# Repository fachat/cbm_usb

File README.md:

# cbm_usb
USB solution for the Commodore Userport

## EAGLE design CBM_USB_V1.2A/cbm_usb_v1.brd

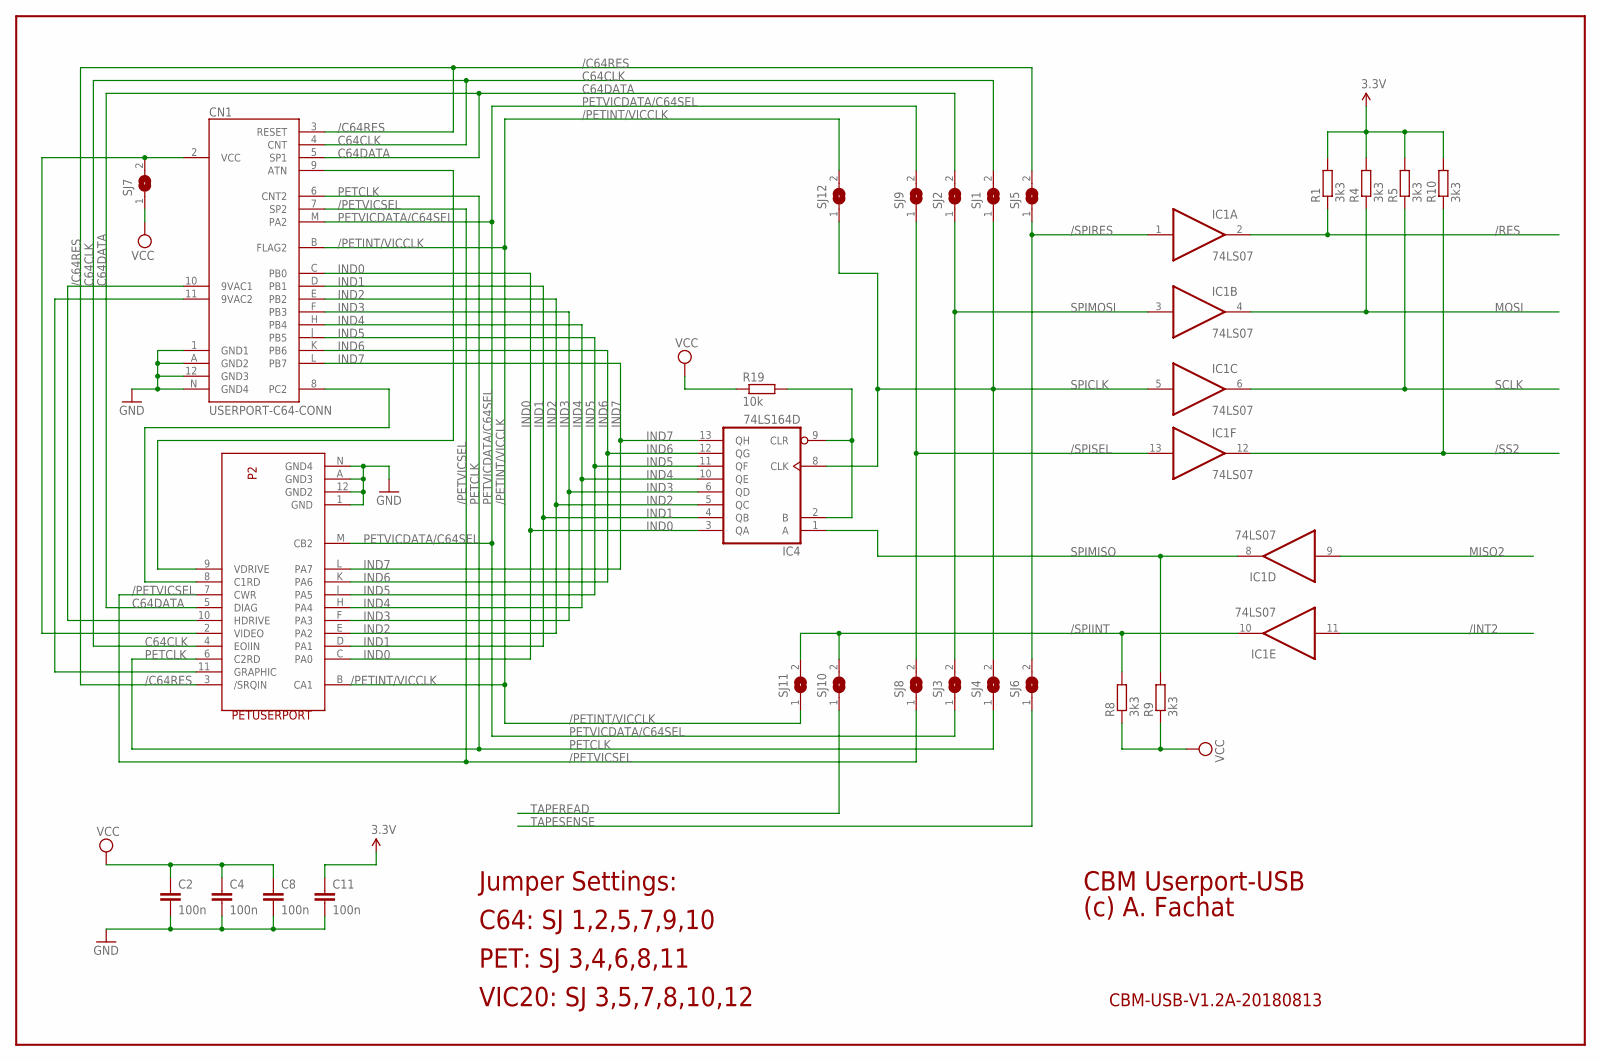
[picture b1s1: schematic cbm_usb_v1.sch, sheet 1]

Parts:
C2, C4, C8, C11: 100n; C050-025X075
CN1: USERPORT-C64-CONN; UPS24CONN
IC1: 74LS07; SO14
IC4: 74LS164D; SO14
P2: PETUSERPORT; FLAT24
R1, R4, R5, R8, R9, R10: 3k3; 0204/7
R19: 10k; 0204/7
SJ1, SJ2, SJ3, SJ4, SJ5, SJ6, SJ7, SJ8, SJ9, SJ10, SJ11, SJ12: SJW

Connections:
3.3V: C11.1, R1.2, R4.2, R5.2, R10.2; also elsewhere on the board
/C64RES: CN1.3 (RESET), P2.3 (/SRQIN), SJ5.2
/INT2: IC1.11 (I); also elsewhere on the board
/PETINT/VICCLK: CN1.B (FLAG2), P2.B (CA1), SJ11.1, SJ12.2
/PETVICSEL: CN1.7 (SP2), P2.7 (CWR), SJ8.1
/RES: IC1.2 (O), R1.1; also elsewhere on the board
/SPIINT: IC1.10 (O), R8.2, SJ10.2, SJ11.2
/SPIRES: IC1.1 (I), SJ5.1, SJ6.2
/SPISEL: IC1.13 (I), SJ8.2, SJ9.1
/SS2: IC1.12 (O), R10.1; also elsewhere on the board
C64CLK: CN1.4 (CNT), P2.4 (EOIIN), SJ1.2
C64DATA: CN1.5 (SP1), P2.5 (DIAG), SJ2.2
GND: C2.2, C4.2, C8.2, C11.2, CN1.1 (GND1), CN1.12 (GND3), CN1.A (GND2), CN1.N (GND4), IC1.7 (GND), IC4.7 (GND), P2.1 (GND), P2.12 (GND2), P2.A (GND3), P2.N (GND4); also elsewhere on the board
IND0: CN1.C (PB0), IC4.3 (QA), P2.C (PA0)
IND1: CN1.D (PB1), IC4.4 (QB), P2.D (PA1)
IND2: CN1.E (PB2), IC4.5 (QC), P2.E (PA2)
IND3: CN1.F (PB3), IC4.6 (QD), P2.F (PA3)
IND4: CN1.H (PB4), IC4.10 (QE), P2.H (PA4)
IND5: CN1.J (PB5), IC4.11 (QF), P2.J (PA5)
IND6: CN1.K (PB6), IC4.12 (QG), P2.K (PA6)
IND7: CN1.L (PB7), IC4.13 (QH), P2.L (PA7)
MISO2: IC1.9 (I); also elsewhere on the board
MOSI: IC1.4 (O), R4.1; also elsewhere on the board
unnamed: CN1.10 (9VAC1), P2.10 (HDRIVE)
unnamed: CN1.11 (9VAC2), P2.11 (GRAPHIC)
unnamed: CN1.2 (VCC), P2.2 (VIDEO), SJ7.2
unnamed: CN1.8 (PC2), P2.8 (C1RD)
unnamed: CN1.9 (ATN), P2.9 (VDRIVE)
unnamed: IC4.2 (B), IC4.9 (CLR), R19.2
PETCLK: CN1.6 (CNT2), P2.6 (C2RD), SJ4.1
PETVICDATA/C64SEL: CN1.M (PA2), P2.M (CB2), SJ3.1, SJ9.2
SCLK: IC1.6 (O), R5.1; also elsewhere on the board
SPICLK: IC1.5 (I), IC4.8 (CLK), SJ1.1, SJ4.2, SJ12.1
SPIMISO: IC1.8 (O), IC4.1 (A), R9.2
SPIMOSI: IC1.3 (I), SJ2.1, SJ3.2
TAPEREAD: SJ10.1; also elsewhere on the board
TAPESENSE: SJ6.1; also elsewhere on the board
VCC: C2.1, C4.1, C8.1, IC1.14 (VCC), IC4.14 (VCC), R8.1, R9.1, R19.1, SJ7.1; also elsewhere on the board

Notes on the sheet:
CBM-USB-V1.2A-20180813
CBM Userport-USB
(c) A. Fachat
Jumper Settings:
C64: SJ 1,2,5,7,9,10
PET: SJ 3,4,6,8,11
VIC20: SJ 3,5,7,8,10,12

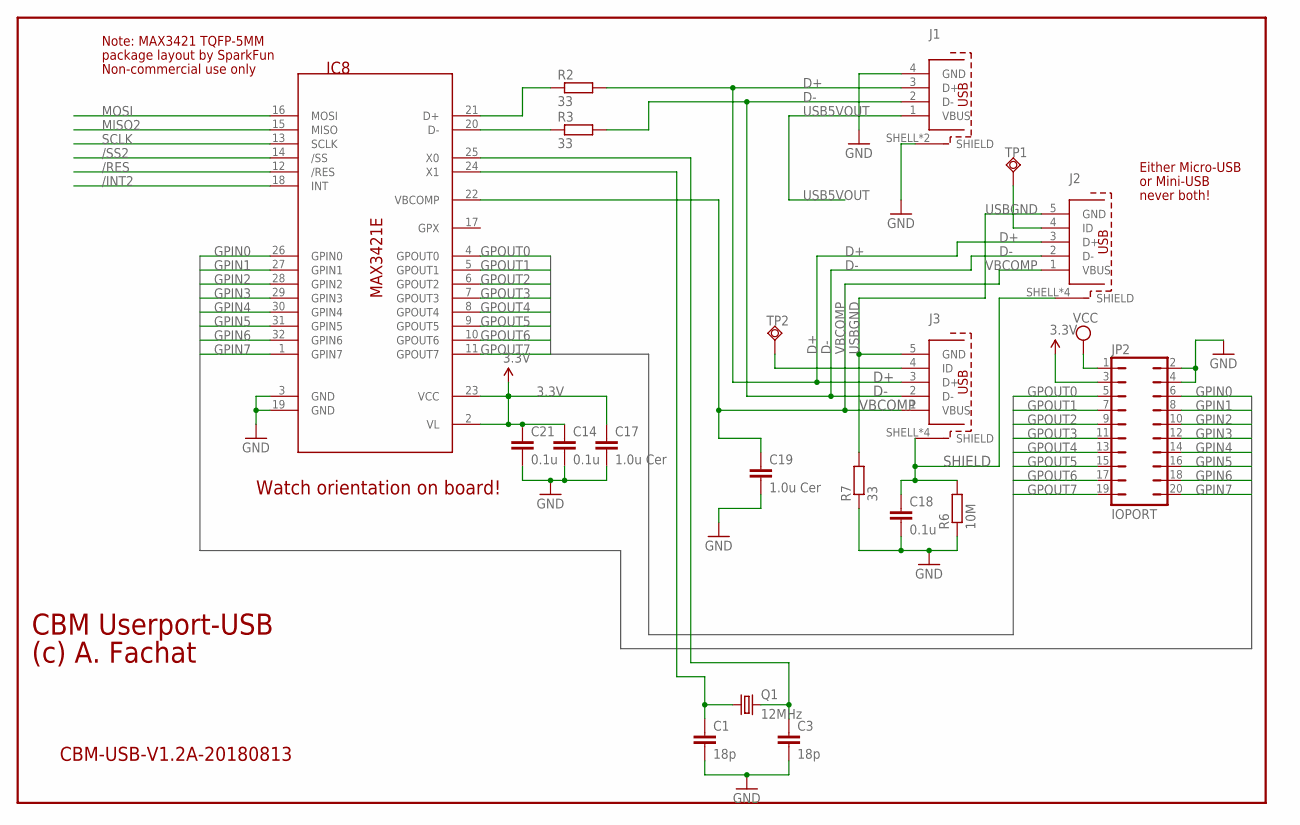
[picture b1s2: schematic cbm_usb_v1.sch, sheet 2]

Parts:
C1, C3: 18p; C050-025X075
C14, C18, C21: 0.1u; C050-025X075
C17, C19: 1.0u Cer; C050-024X044
IC8: MAX3421E; TQFP32-5MM
J1: 614004190021
J2: 629105150521
J3: 65100516121
JP2: IOPORT; JP10Q
Q1: 12MHz; HC49U70
R2, R3, R7: 33; 0204/7
R6: 10M; 0204/7
TP1, TP2: TPSQTP14SQ; TP14SQ

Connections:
3.3V: C14.1, C17.1, C21.1, IC8.2 (VL), IC8.23 (VCC), JP2.3; also elsewhere on the board
12MHZ: C1.1, IC8.24 (X1), Q1.1
/INT2: IC8.18 (INT); also elsewhere on the board
/RES: IC8.12 (/RES); also elsewhere on the board
/SS2: IC8.14 (/SS); also elsewhere on the board
D+: J1.3 (D+), J2.3 (D+), J3.3 (D+), R2.2
D-: J1.2 (D-), J2.2 (D-), J3.2 (D-), R3.2
GND: C1.2, C3.2, C14.2, C17.2, C18.2, C19.2, C21.2, IC8.3 (GND), IC8.19 (GND), J1.4 (GND), J1.SHELL (SHIELD), J1.SHELL1 (SHIELD), JP2.2, JP2.4, R6.1, R7.1; also elsewhere on the board
GPIN0: IC8.26 (GPIN0), JP2.6
GPIN1: IC8.27 (GPIN1), JP2.8
GPIN2: IC8.28 (GPIN2), JP2.10
GPIN3: IC8.29 (GPIN3), JP2.12
GPIN4: IC8.30 (GPIN4), JP2.14
GPIN5: IC8.31 (GPIN5), JP2.16
GPIN6: IC8.32 (GPIN6), JP2.18
GPIN7: IC8.1 (GPIN7), JP2.20
GPOUT0: IC8.4 (GPOUT0), JP2.5
GPOUT1: IC8.5 (GPOUT1), JP2.7
GPOUT2: IC8.6 (GPOUT2), JP2.9
GPOUT3: IC8.7 (GPOUT3), JP2.11
GPOUT4: IC8.8 (GPOUT4), JP2.13
GPOUT5: IC8.9 (GPOUT5), JP2.15
GPOUT6: IC8.10 (GPOUT6), JP2.17
GPOUT7: IC8.11 (GPOUT7), JP2.19
MISO2: IC8.15 (MISO); also elsewhere on the board
MOSI: IC8.16 (MOSI); also elsewhere on the board
unnamed: IC8.20 (D-), R3.1
unnamed: IC8.21 (D+), R2.1
unnamed: C3.1, IC8.25 (X0), Q1.2
unnamed: J2.4 (ID), TP1.TP
unnamed: J3.4 (ID), TP2.TP
SCLK: IC8.13 (SCLK); also elsewhere on the board
SHIELD: C18.1, J2.SHELL (SHIELD), J2.SHELL1 (SHIELD), J2.SHELL2 (SHIELD), J2.SHELL3 (SHIELD), J3.SHELL (SHIELD), J3.SHELL1 (SHIELD), J3.SHELL2 (SHIELD), J3.SHELL3 (SHIELD), R6.2
USB5VOUT: J1.1 (VBUS); also elsewhere on the board
USBGND: J2.5 (GND), J3.5 (GND), R7.2
VBCOMP: C19.1, IC8.22 (VBCOMP), J2.1 (VBUS), J3.1 (VBUS)
VCC: JP2.1; also elsewhere on the board

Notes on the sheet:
CBM-USB-V1.2A-20180813
CBM Userport-USB
(c) A. Fachat
Either Micro-USB
or Mini-USB
never both!
Watch orientation on board!
Note: MAX3421 TQFP-5MM
Non-commercial use only
package layout by SparkFun

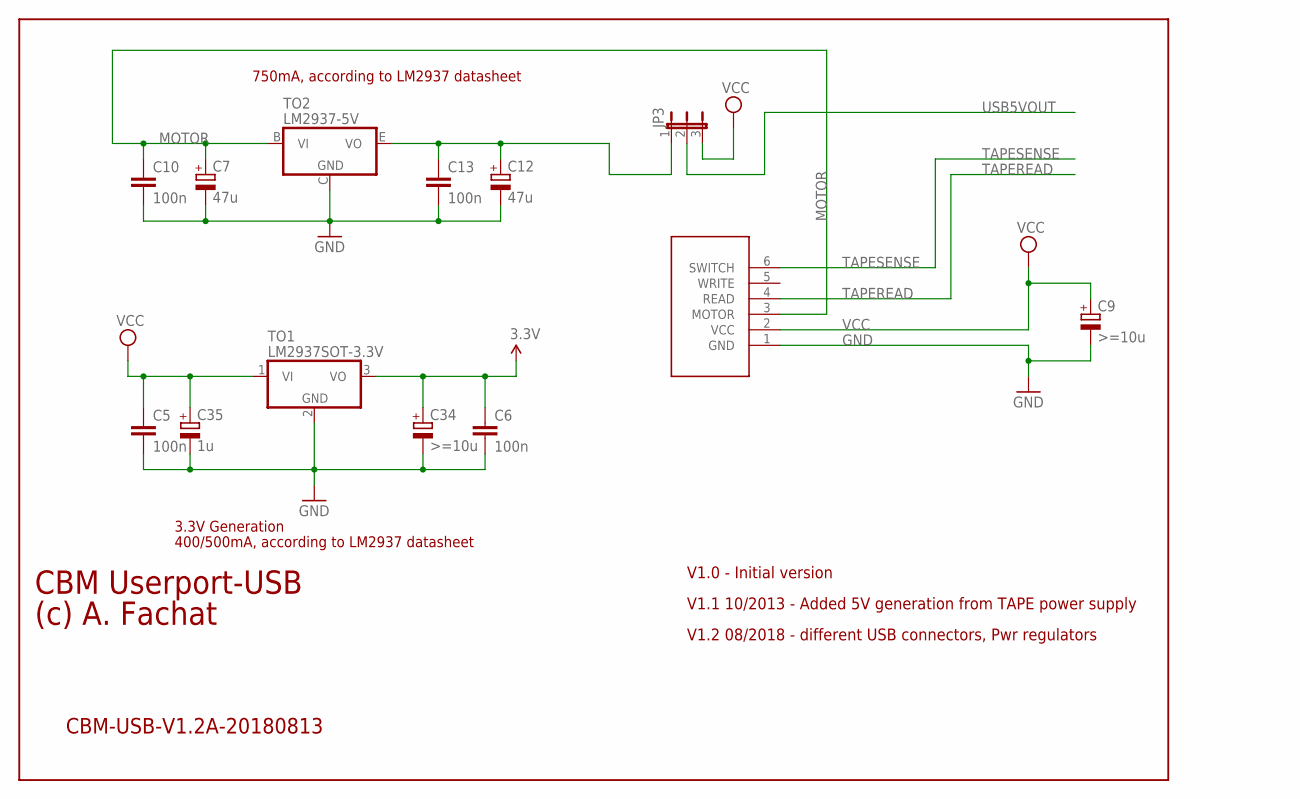
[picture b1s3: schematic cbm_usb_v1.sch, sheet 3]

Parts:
C5, C6: 100n; C050-025X075
C7, C12: 47u; E3,5-8
C9: >=10u; E5-10,5
C10, C13: 100n; C050-030X075
C34: >=10u; E5-8,5
C35: 1u; E5-8,5
JP3: JP2E; JP2
P3: CBMTAPE; JP6
TO1: LM2937SOT-3.3V; SOT223
TO2: LM2937-5V; TO220H

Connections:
3.3V: C6.1, C34.+, TO1.3 (VO); also elsewhere on the board
GND: C5.2, C6.2, C7.-, C9.-, C10.2, C12.-, C13.2, C34.-, C35.-, P3.1 (GND), TO1.2 (GND), TO2.C (GND); also elsewhere on the board
MOTOR: C7.+, C10.1, P3.3 (MOTOR), TO2.B (VI)
unnamed: C12.+, C13.1, JP3.1, TO2.E (VO)
TAPEREAD: P3.4 (READ); also elsewhere on the board
TAPESENSE: P3.6 (SWITCH); also elsewhere on the board
USB5VOUT: JP3.2; also elsewhere on the board
VCC: C5.1, C9.+, C35.+, JP3.3, P3.2 (VCC), TO1.1 (VI); also elsewhere on the board

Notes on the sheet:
3.3V Generation
400/500mA, according to LM2937 datasheet
CBM-USB-V1.2A-20180813
CBM Userport-USB
(c) A. Fachat
V1.0 - Initial version
V1.1 10/2013 - Added 5V generation from TAPE power supply
V1.2 08/2018 - different USB connectors, Pwr regulators
750mA, according to LM2937 datasheet

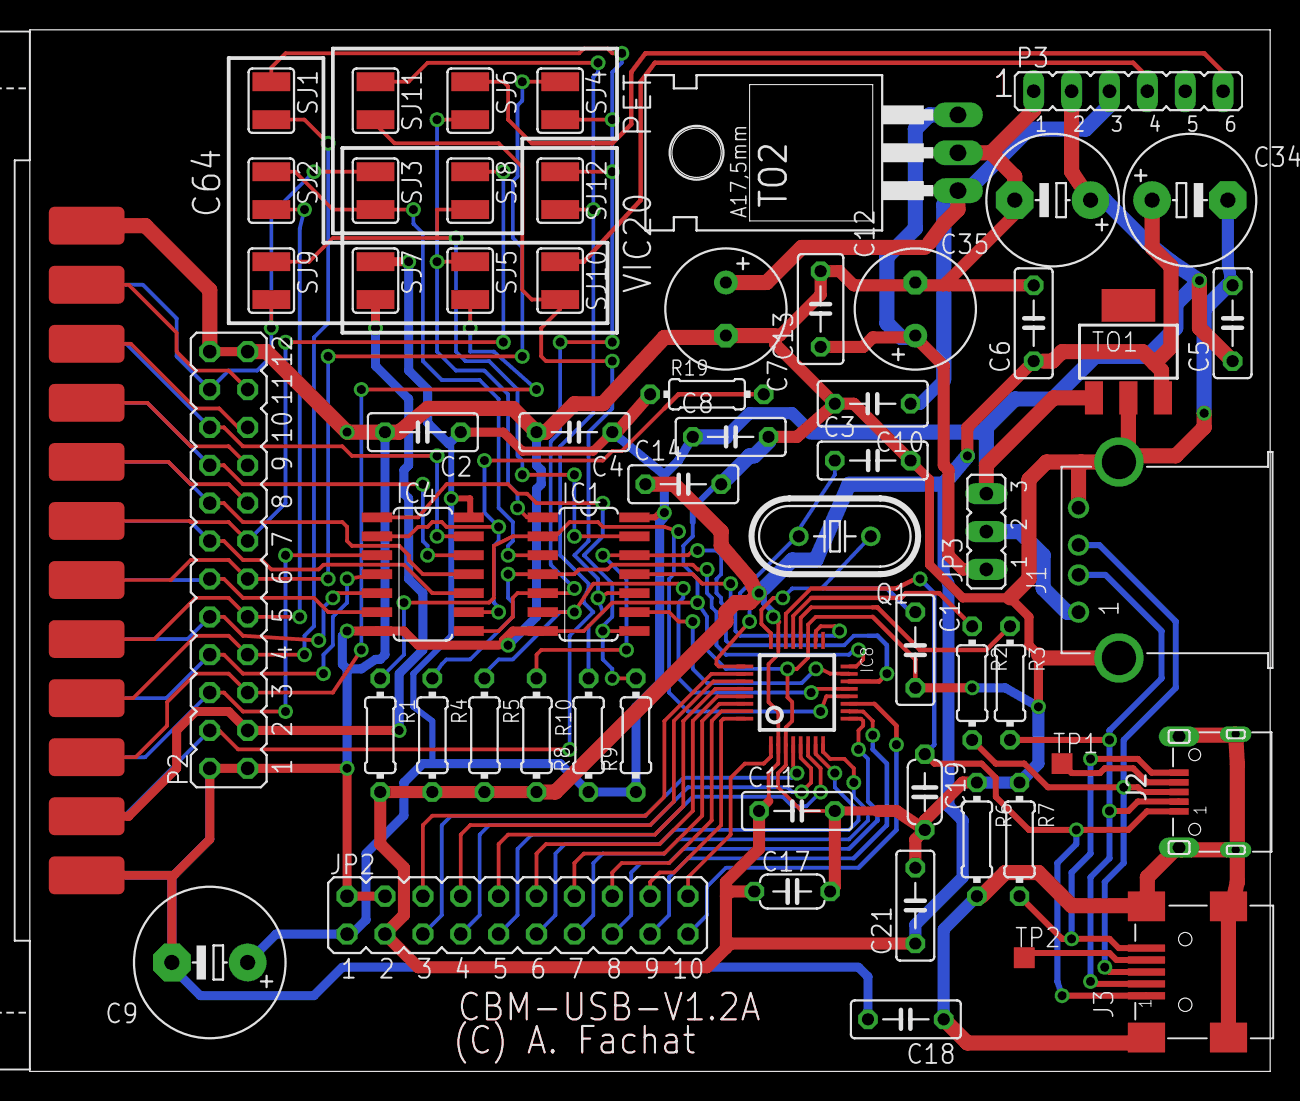
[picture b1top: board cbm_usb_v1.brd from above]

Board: 2 copper layers, 83.2 x 69.8 mm, 59 parts (0 on the bottom side), 68 nets.

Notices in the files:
parts and their libraries:
Wuerth_InputOutputIO: Copyright: Würth Elektronik
